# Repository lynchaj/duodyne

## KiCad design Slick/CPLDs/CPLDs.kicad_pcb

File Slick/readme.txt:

The processor.Z80 board is the central processor for the duodyne system.  It uses a Z80 8-bit CPU and includes dual-DMA channels.  It supports Interrupt Mode 2 (IM2) and an extended memory mapper.

Known Issues
1. Missing pull-up resistors on ~DREQ0 and ~DREQ1

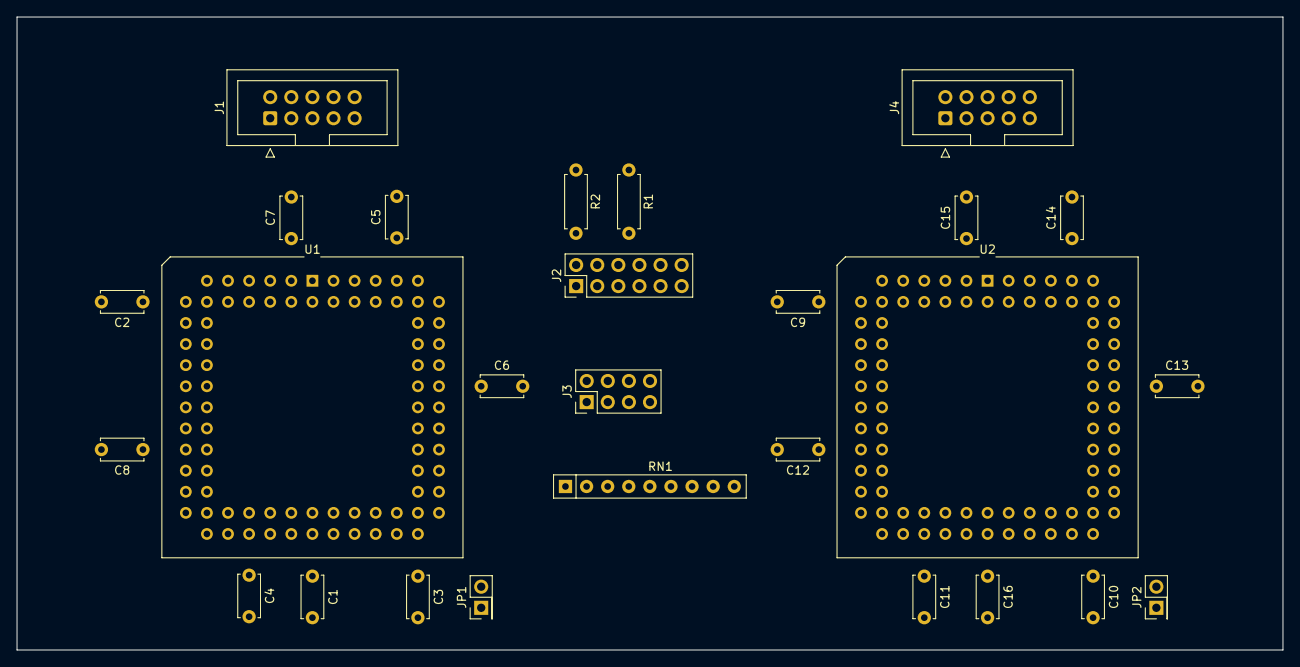
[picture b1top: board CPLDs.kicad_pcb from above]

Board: 2 copper layers, 152.4 x 76.2 mm, 27 parts (0 on the bottom side), 33 nets, no tracks yet.

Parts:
C1, C2, C3, C4, C5, C6, C7, C8, C9, C10, C11, C12, C13, C14, C15, C16: 0.1u; C_Disc_D5.0mm_W2.5mm_P5.00mm
J1: JTAG-1; IDC-Header_2x05_P2.54mm_Vertical
J2: Conn_02x06_Odd_Even; PinHeader_2x06_P2.54mm_Vertical
J3: Conn_02x04_Odd_Even; PinHeader_2x04_P2.54mm_Vertical
J4: JTAG-2; IDC-Header_2x05_P2.54mm_Vertical
JP1, JP2: Jumper_2_Bridged; PinHeader_2x01_P2.54mm_Vertical
R1, R2: 10K; R_Axial_DIN0207_L6.3mm_D2.5mm_P7.62mm_Horizontal
RN1: 10K; R_Array_SIP9
U1, U2: EPM7064S-PLCC-84; PLCC-84_THT-Socket

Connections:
/VCC: JP1.1 (A), JP2.1 (A)
/VCC1: C1.1, C2.1, C3.1, C4.1, C5.1, C6.1, C7.1, C8.1, J1.4, JP1.2 (B), U1.3 (VCCINT), U1.13 (VCCIO), U1.26 (VCCIO), U1.38 (VCCIO), U1.43 (VCCINT), U1.53 (VCCIO), U1.66 (VCCIO), U1.78 (VCCIO)
/VCC2: C9.1, C10.1, C11.1, C12.1, C13.1, C14.1, C15.1, C16.1, J4.4, JP2.2 (B), R1.1, R2.1, RN1.1 (common), U2.3 (VCCINT), U2.13 (VCCIO), U2.26 (VCCIO), U2.38 (VCCIO), U2.43 (VCCINT), U2.53 (VCCIO), U2.66 (VCCIO), U2.78 (VCCIO)
CPU-A1: U1.48 (I/O_4C), U2.34 (I/O_7B)
CPU-A2: U1.25 (I/O_14B), U2.20 (I/O_3A)
CPU-D0: U1.75 (I/O_11D), U2.37 (I/O_4B), U2.46 (I/O_3C)
GND: C1.2, C2.2, C3.2, C4.2, C5.2, C6.2, C7.2, C8.2, C9.2, C10.2, C11.2, C12.2, C13.2, C14.2, C15.2, C16.2, J1.2, J1.10, J4.2, J4.10, U1.2 (OE2/GCLK2), U1.7 (GND), U1.19 (GND), U1.32 (GND), U1.42 (GND), U1.47 (GND), U1.59 (GND), U1.72 (GND), U1.82 (GND), U2.2 (OE2/GCLK2), U2.7 (GND), U2.19 (GND), U2.32 (GND), U2.42 (GND), U2.47 (GND), U2.59 (GND), U2.72 (GND), U2.82 (GND), U2.83 (GCLK1)
IO-SEL: U1.50 (I/O_6C), U2.5 (I/O_15A)
Q2: J2.12, RN1.9 (R8), U2.15 (I/O_7A)
Q3: J2.10, RN1.8 (R7), U2.16 (I/O_6A)
Q4: J2.8, RN1.7 (R6), U2.69 (I/O_6D)
Q5: J2.6, RN1.6 (R5), U2.18 (I/O_4A)
Q6: J2.4, R1.2, U2.81 (I/O_16D)
Q7: J2.2, R2.2, U2.80 (I/O_15D)
R4: J3.8, RN1.5 (R4), U2.25 (I/O_14B)
R5: J3.6, RN1.4 (R3), U2.56 (I/O_12C)
R6: J3.4, RN1.3 (R2), U2.58 (I/O_14C)
R7: J3.2, RN1.2 (R1), U2.11 (I/O_10A)
TCK-1: J1.1, U1.62 (TCK-I/O_16C)
TCK-2: J4.1, U2.62 (TCK-I/O_16C)
TDI-1: J1.9, U1.14 (TDI-I/O_8A)
TDI-2: J4.9, U2.14 (TDI-I/O_8A)
TDO-1: J1.3, U1.71 (TDO-I/O_8D)
TDO-2: J4.3, U2.71 (TDO-I/O_8D)
TMS-1: J1.5, U1.23 (TMS-I/O_16B)
TMS-2: J4.5, U2.23 (TMS-I/O_16B)
ZERO: J2.1, J2.3, J2.5, J2.7, J2.9, J2.11, J3.1, J3.3, J3.5, J3.7
~CPU-IORQ: U1.58 (I/O_14C), U2.61 (I/O_16C)
~CPU-M1: U1.80 (I/O_15D), U2.60 (I/O_15C)
~CPU-RESET: U1.1 (GCLRn), U2.1 (GCLRn)
~CPU-WR: U1.79 (I/O_14D), U2.68 (I/O_5D)
~CS-MAP: U1.27 (I/O_13B), U2.36 (I/O_5B)
~FP-LATCH: U1.24 (I/O_15B), U2.9 (I/O_12A)

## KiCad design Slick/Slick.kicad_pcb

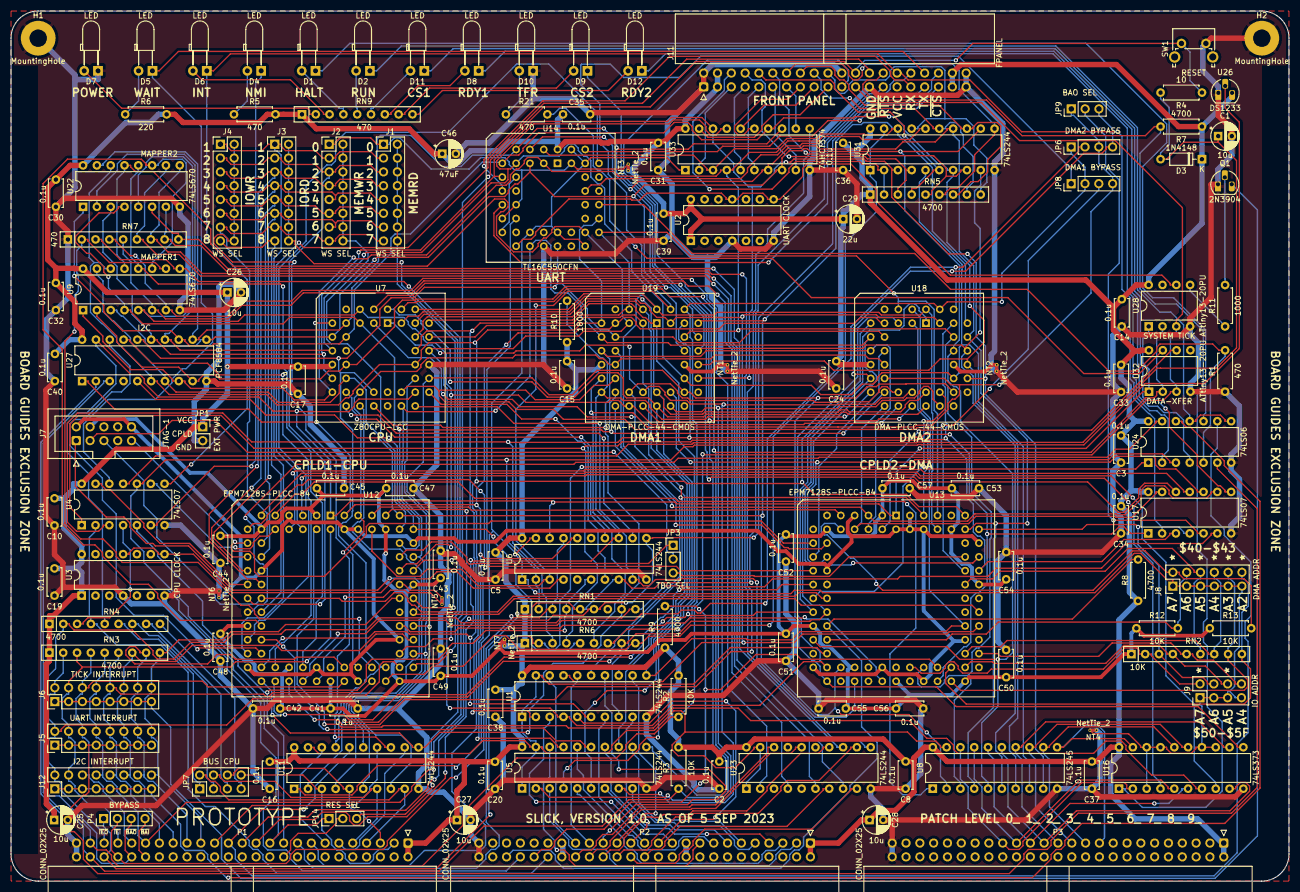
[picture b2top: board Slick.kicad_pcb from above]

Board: 2 copper layers, 235.0 x 160.0 mm, 139 parts (0 on the bottom side), 244 nets.

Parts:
C1, C25, C26, C27, C28: 10u; CP_Radial_D5.0mm_P2.50mm
C2, C3, C5, C8, C10, C14, C15, C16, C17, C19, C20, C24, C30, C31, C32, C33, C34, C35, C36, C37, C38, C39, C40, C41, C42, C43, C44, C45, C47, C48, C49, C50, C51, C52, C53, C54, C55, C56, C57: 0.1u; C_Disc_D5.0mm_W2.5mm_P5.00mm
C29: 22u; CP_Radial_D5.0mm_P2.50mm
C46: 47uF; CP_Radial_D5.0mm_P2.50mm
D1, D2, D4, D5, D6, D7, D8, D9, D10, D11, D12: LED; LED_D3.0mm_Horizontal_O3.81mm_Z2.0mm
D3: 1N4148; D_DO-35_SOD27_P7.62mm_Horizontal
H1, H2: MountingHole; MountingHole_3.2mm_M3_Pad
J1, J2, J3, J4: WS SEL; PinHeader_2x08_P2.54mm_Vertical
J5: UART INTERRUPT; PinHeader_2x08_P2.54mm_Vertical
J6: TICK INTERRUPT; PinHeader_2x08_P2.54mm_Vertical
J7: JTAG-1; IDC-Header_2x05_P2.54mm_Vertical
J8: DMA ADDR; PinHeader_2x06_P2.54mm_Vertical
J9: IO ADDR; PinHeader_2x04_P2.54mm_Vertical
J11: FPANEL; IDC-Header_2x20_P2.54mm_Horizontal
J12: I2C INTERRUPT; PinHeader_2x08_P2.54mm_Vertical
JP1: EXT PWR; PinHeader_2x01_P2.54mm_Vertical
JP3: TDO SEL; PinHeader_1x03_P2.54mm_Vertical
JP6: DMA2 BYPASS; PinHeader_1x04_P2.54mm_Vertical
JP7: BUS CPU; PinHeader_2x04_P2.54mm_Vertical
JP8: DMA1 BYPASS; PinHeader_1x04_P2.54mm_Vertical
JP9: BAO SEL; PinHeader_1x03_P2.54mm_Vertical
JP14: RES SEL; PinHeader_1x03_P2.54mm_Vertical
NT1, NT2, NT3, NT4, NT5, NT6, NT7: NetTie_2; NetTie-2_THT_Pad0.3mm
P1, P2, P3: CONN_02X25; IDC-Header_2x25_P2.54mm_Horizontal
P4: BYPASS; PinHeader_1x04_P2.54mm_Vertical
Q1: 2N3904; TO-92_HandSolder
R1, R5, R21: 470; R_Axial_DIN0207_L6.3mm_D2.5mm_P7.62mm_Horizontal
R2, R3, R12, R13: 10K; R_Axial_DIN0207_L6.3mm_D2.5mm_P7.62mm_Horizontal
R4: 10; R_Axial_DIN0207_L6.3mm_D2.5mm_P7.62mm_Horizontal
R6: 220; R_Axial_DIN0207_L6.3mm_D2.5mm_P7.62mm_Horizontal
R7, R8, R9: 4700; R_Axial_DIN0207_L6.3mm_D2.5mm_P7.62mm_Horizontal
R10: 1800; R_Axial_DIN0207_L6.3mm_D2.5mm_P7.62mm_Horizontal
R11: 1000; R_Axial_DIN0207_L6.3mm_D2.5mm_P7.62mm_Horizontal
RN1, RN3, RN4, RN5, RN6: 4700; R_Array_SIP9
RN2: 10K; R_Array_SIP9
RN7, RN9: 470; R_Array_SIP9
SW1: RESET; SW_Tactile_SPST_Angled_PTS645Vx58-2LFS
U1, U5, U6, U11, U23, U31: 74LS244; DIP-20_W7.62mm
U2: UART CLOCK; DIP-14_W7.62mm
U3: CPU CLOCK; DIP-14_W7.62mm
U4, U17: 74LS07; DIP-14_W7.62mm
U7: Z80CPU-LCC; PLCC-44_THT-Socket
U8: 74LS245; DIP-20_W7.62mm
U9, U22: 74LS670; DIP-16_W7.62mm
U12, U13: EPM7128S-PLCC-84; PLCC-84_THT-Socket
U14: TL16C550CFN; PLCC-44_THT-Socket
U16: 74LS373; DIP-20_W7.62mm
U18, U19: DMA-PLCC-44-CMOS; PLCC-44_THT-Socket
U24: 74LS06; DIP-14_W7.62mm
U26: DS1233; TO-92L_HandSolder
U27: PCF8584; DIP-20_W7.62mm
U28, U32: ATtiny13-20PU; DIP-8_W7.62mm
U33: 74HCT374; DIP-20_W7.62mm

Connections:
1WS: J1.3, J2.3, J3.1, J4.1, U12.30 (I/O_5C)
2WS: J1.5, J2.5, J3.3, J4.3, U12.22 (I/O_1B)
3WS: J1.7, J2.7, J3.5, J4.5, U12.21 (I/O_3B)
4WS: J1.9, J2.9, J3.7, J4.7, U12.18 (I/O_8B)
5WS: J1.11, J2.11, J3.9, J4.9, U12.17 (I/O_9B)
6WS: J1.13, J2.13, J3.11, J4.11, U12.16 (I/O_11B)
7WS: J1.15, J2.15, J3.13, J4.13, U12.15 (I/O_13B)
8WS: J3.15, J4.15, U12.25 (I/O_13C)
10KA: C1.1, D3.2 (A), R4.2, U4.11
470A: D7.2 (A), RN9.2 (R1)
470B: D6.2 (A), RN9.3 (R2)
470C: D1.2 (A), RN9.4 (R3)
470D: D2.2 (A), RN9.5 (R4)
470E: D11.2 (A), RN9.6 (R5)
470F: D8.2 (A), RN9.7 (R6)
470G: D9.2 (A), RN9.8 (R7)
470H: D12.2 (A), RN9.9 (R8)
+12V: P2.19, P2.20
-12V: P2.37, P2.38
/CPLDs/VCC-CPLD: C41.1, C42.1, C43.1, C44.1, C45.1, C47.1, C48.1, C49.1, C50.1, C51.1, C52.1, C53.1, C54.1, C55.1, C56.1, C57.1, J7.4, NT7.2, R12.1, R13.1, RN2.1 (common), U12.3 (VCCINT), U12.13 (VCCIO), U12.26 (VCCIO), U12.38 (VCCIO), U12.43 (VCCINT), U12.53 (VCCIO), U12.66 (VCCIO), U12.78 (VCCIO), U13.3 (VCCINT), U13.13 (VCCIO), U13.26 (VCCIO), U13.38 (VCCIO), U13.43 (VCCINT), U13.53 (VCCIO), U13.66 (VCCIO), U13.78 (VCCIO)
/DMA/GND-DMA1: NT1.2, U19.34 (GND)
/DMA/GND-DMA2: NT2.2, U18.34 (GND)
/fpanel/FP-D0: J11.6, RN5.2 (R1), U31.2 (I0a)
/fpanel/FP-D1: J11.8, RN5.3 (R2), U31.4 (I1a)
/fpanel/FP-D2: J11.10, RN5.4 (R3), U31.6 (I2a)
/fpanel/FP-D3: J11.12, RN5.5 (R4), U31.8 (I3a)
/fpanel/FP-D4: J11.14, RN5.6 (R5), U31.11 (I0b)
/fpanel/FP-D5: J11.16, RN5.7 (R6), U31.13 (I1b)
/fpanel/FP-D6: J11.18, RN5.8 (R7), U31.15 (I2b)
/fpanel/FP-D7: J11.20, RN5.9 (R8), U31.17 (I3b)
A0: P2.35, U1.18 (O0a)
A1: P2.33, U1.16 (O1a)
A2: P2.31, U1.14 (O2a)
A3: P2.29, U1.12 (O3a)
A4: P2.27, U1.9 (O0b)
A5: P2.25, U1.7 (O1b)
A6: P2.23, U1.5 (O2b)
A7: P2.21, U1.3 (O3b)
A8: P2.17, U5.18 (O0a)
A9: P2.15, U5.16 (O1a)
A10: P2.13, U5.14 (O2a)
A11: P2.11, U5.12 (O3a)
A12: P2.9, U5.9 (O0b)
A13: P2.7, U5.7 (O1b)
A14: P2.5, U5.5 (O2b)
A15: P2.3, U5.3 (O3b)
A16: P2.36, U23.18 (O0a)
A17: P2.34, U23.16 (O1a)
A18: P2.32, U23.14 (O2a)
A19: P2.30, U23.12 (O3a)
A20: P2.28, U23.9 (O0b)
A21: P2.26, U23.7 (O1b)
CLK: P1.15, U6.16 (O1a), U7.7 (CLK), U12.83 (GCLK1), U18.8 (CLK), U19.8 (CLK), U27.1 (CLK)
CPU-A0: U1.2 (I0a), U7.34 (A0), U9.14 (Wa), U13.75 (I/O_6H), U14.31 (A0), U18.7 (A0), U19.7 (A0), U22.14 (Wa), U27.6 (A0)
CPU-A1: U1.4 (I1a), U7.35 (A1), U9.13 (Wb), U12.64 (I/O_3G), U13.34 (I/O_13D), U14.30 (A1), U18.5 (A1), U19.5 (A1), U22.13 (Wb)
CPU-A2: U1.6 (I2a), U7.36 (A2), U12.34 (I/O_13D), U13.79 (I/O_13H), U14.29 (A2), U18.4 (A2), U19.4 (A2)
CPU-A3: U1.8 (I3a), U7.37 (A3), U13.81 (I/O_16H), U18.3 (A3), U19.3 (A3)
CPU-A4: U1.11 (I0b), U7.38 (A4), U13.61 (I/O_14F), U18.2 (A4), U19.2 (A4)
CPU-A5: U1.13 (I1b), U7.39 (A5), U13.24 (I/O_14C), U18.1 (A5), U19.1 (A5)
CPU-A6: U1.15 (I2b), U7.40 (A6), U13.80 (I/O_14H), U18.44 (A6), U19.44 (A6)
CPU-A7: U1.17 (I3b), U7.41 (A7), U13.60 (I/O_13F), U18.43 (A7), U19.43 (A7)
CPU-A8: U5.2 (I0a), U7.42 (A8), U18.26 (A8), U19.26 (A8)
CPU-A9: U5.4 (I1a), U7.43 (A9), U18.25 (A9), U19.25 (A9)
CPU-A10: U5.6 (I2a), U7.44 (A10), U18.24 (A10), U19.24 (A10)
CPU-A11: U5.8 (I3a), U7.1 (A11), U18.23 (A11), U19.23 (A11)
CPU-A12: U5.11 (I0b), U7.2 (A12), U18.22 (A12), U19.22 (A12)
CPU-A13: U5.13 (I1b), U7.3 (A13), U18.21 (A13), U19.21 (A13)
CPU-A14: U7.4 (A14), U9.5 (Ra), U12.69 (I/O_11G), U18.20 (A14), U19.20 (A14), U22.5 (Ra)
CPU-A15: U7.5 (A15), U9.4 (Rb), U12.73 (I/O_3H), U18.19 (A15), U19.19 (A15), U22.4 (Rb)
CPU-D0: U7.16 (D0), U8.2 (A0), U9.15 (D1), U12.75 (I/O_6H), U13.36 (I/O_9D), U14.2 (D0), U18.39 (D0), U19.39 (D0), U27.7 (D0), U31.18 (O0a), U33.3 (D0)
CPU-D1: U7.17 (D1), U8.3 (A1), U9.1 (D2), U13.48 (I/O_8E), U14.3 (D1), U18.38 (D1), U19.38 (D1), U27.8 (D1), U31.16 (O1a), U33.4 (D1)
CPU-D2: U7.14 (D2), U8.4 (A2), U9.2 (D3), U13.76 (I/O_8H), U14.4 (D2), U18.37 (D2), U19.37 (D2), U27.9 (D2), U31.14 (O2a), U33.7 (D2)
CPU-D3: U7.9 (D3), U8.5 (A3), U9.3 (D4), U13.28 (I/O_8C), U14.5 (D3), U18.36 (D3), U19.36 (D3), U27.11 (D3), U31.12 (O3a), U33.8 (D3)
CPU-D4: U7.8 (D4), U8.6 (A4), U14.6 (D4), U18.35 (D4), U19.35 (D4), U22.15 (D1), U27.12 (D4), U31.9 (O0b), U33.13 (D4)
CPU-D5: U7.10 (D5), U8.7 (A5), U14.7 (D5), U18.33 (D5), U19.33 (D5), U22.1 (D2), U27.13 (D5), U31.7 (O1b), U33.14 (D5)
CPU-D6: U7.11 (D6), U8.8 (A6), U14.8 (D6), U18.32 (D6), U19.32 (D6), U22.2 (D3), U27.14 (D6), U31.5 (O2b), U33.17 (D6)
CPU-D7: U7.15 (D7), U8.9 (A7), U14.9 (D7), U18.31 (D7), U19.31 (D7), U22.3 (D4), U27.15 (D7), U31.3 (O3b), U33.18 (D7)
D0: P3.33, U8.18 (B0), U16.2 (O0)
D1: P3.31, U8.17 (B1), U16.5 (O1)
D2: P3.29, U8.16 (B2), U16.6 (O2)
D3: P3.27, U8.15 (B3), U16.9 (O3)
D4: P3.25, U8.14 (B4), U16.12 (O4)
D5: P3.23, U8.13 (B5), U16.15 (O5)
D6: P3.21, U8.12 (B6), U16.16 (O6)
D7: P3.19, U8.11 (B7), U16.19 (O7)
DATA-DIR: U8.1 (A->B), U12.9 (I/O_8A)
DATA-XFER: U13.4 (I/O_16A), U32.6 (PB1)
DMA-RDY1: U13.17 (I/O_9B), U19.27 (RDY), U24.3
DMA-RDY2: U13.22 (I/O_1B), U18.27 (RDY), U24.1
FP-LATCH-WR: U12.37 (I/O_8D), U33.11 (Cp)
GND: C1.2, C2.2, C3.2, C5.2, C8.2, C10.2, C14.2, C15.2, C16.2, C17.2, C19.2, C20.2, C24.2, C25.2, C26.2, C27.2, C28.2, C29.2, C30.2, C31.2, C32.2, C33.2, C34.2, C35.2, C36.2, C37.2, C38.2, C39.2, C40.2, C41.2, C42.2, C43.2, C44.2, C45.2, C46.2, C47.2, C48.2, C49.2, C50.2, C51.2, C52.2, C53.2, C54.2, C55.2, C56.2, C57.2, D7.1 (K), D10.1 (K), H1.1, H2.1, J11.1, J11.2, J11.22, J11.25, J11.39, J11.40, JP1.2 (B), NT1.1, NT2.1, NT4.1, NT6.2, P1.49, P1.50, P2.49, P2.50, P3.49, P3.50, Q1.1 (E), R1.1, RN7.1 (common), SW1.2, U1.10 (GND), U2.4, U2.7, U3.4, U3.7, U4.7 (GND), U5.10 (GND), U6.10 (GND), U7.33 (GND), U8.10 (GND), U9.8 (GND), U11.10 (GND), U14.22 (GND), U16.10 (GND), U17.7 (GND), U22.8 (GND), U23.10 (GND), U24.7 (GND), U26.1, U27.10 (VSS), U28.4 (GND), U31.10 (GND), U32.4 (GND), U33.10 (GND)
GND-CPLD: J7.2, J7.10, NT6.1, U12.7 (GNDIO), U12.19 (GNDIO), U12.32 (GNDIO), U12.42 (GNDINT), U12.47 (GNDIO), U12.59 (GNDIO), U12.72 (GNDIO), U12.82 (GNDINT), U12.84 (OE1), U13.2 (OE2/GCLK2), U13.7 (GNDIO), U13.19 (GNDIO), U13.32 (GNDIO), U13.42 (GNDINT), U13.47 (GNDIO), U13.59 (GNDIO), U13.72 (GNDIO), U13.82 (GNDINT), U13.83 (GCLK1), U13.84 (OE1)
I2C-SCL: J11.23, P1.47, R2.1, U27.3 (SCL), U28.3 (PB4), U32.3 (PB4)
I2C-SDA: J11.21, P1.48, R3.1, U27.2 (SDA), U28.2 (PB3), U32.2 (PB3)
IM2-S0: U12.5 (I/O_14A), U16.4 (D1)
IM2-S1: U12.4 (I/O_16A), U16.7 (D2)
IM2-S2: U12.11 (I/O_5A), U16.8 (D3)
INT: R1.2, U14.33 (INTR), U24.5
INT-I2C: U12.24 (I/O_14C), U24.13
IO-SEL: U12.61 (I/O_14F), U13.41 (I/O_1D)
unnamed: D1.1 (K), U24.10
unnamed: D2.1 (K), U24.8, U24.11
unnamed: D4.1 (K), U4.6
unnamed: D4.2 (A), R5.1
unnamed: D5.2 (A), R6.1
unnamed: D8.1 (K), U24.4
unnamed: D9.1 (K), U17.12
unnamed: D10.2 (A), R21.1
unnamed: D11.1 (K), U17.8
unnamed: D12.1 (K), U24.2
unnamed: J5.1, J5.3, J5.5, J5.7, J5.9, J5.11, J5.13, J5.15, U24.6
unnamed: J6.1, J6.3, J6.5, J6.7, J6.9, J6.11, J6.13, J6.15, Q1.3 (C)
unnamed: J11.5, U33.2 (O0)
unnamed: J11.7, U33.5 (O1)
unnamed: J11.9, U33.6 (O2)
unnamed: J11.11, U33.9 (O3)
unnamed: J11.13, U33.12 (O4)
unnamed: J11.15, U33.15 (O5)
unnamed: J11.17, U33.16 (O6)
unnamed: J11.19, U33.19 (O7)
unnamed: J12.1, J12.3, J12.5, J12.7, J12.9, J12.11, J12.13, J12.15, U24.12
unnamed: JP7.1, RN4.6 (R5)
unnamed: JP7.3, RN4.7 (R6)
unnamed: JP7.5, RN4.8 (R7)
unnamed: JP7.7, RN4.9 (R8)
unnamed: JP9.2, U17.5
unnamed: Q1.2 (B), R11.2
unnamed: R11.1, U28.5 (PB0)
unnamed: R21.2, U32.7 (PB2)
unnamed: U14.10 (RCLK), U14.17 (~BAUDOUT)
ONE: J1.1, J2.1, NT3.2, U14.14 (CS0), U14.15 (CS1), U14.43 (~RI)
Q2: J8.12, RN2.9 (R8), U13.52 (I/O_16E)
Q3: J8.10, RN2.8 (R7), U13.51 (I/O_13E)
Q4: J8.8, RN2.7 (R6), U13.57 (I/O_8F)
Q5: J8.6, RN2.6 (R5), U13.67 (I/O_8G)
Q6: J8.4, R12.2, U13.29 (I/O_6C)
Q7: J8.2, R13.2, U13.10 (I/O_6A)
R4: J9.8, RN2.5 (R4), U13.56 (I/O_6F)
R5: J9.6, RN2.4 (R3), U13.55 (I/O_5F)
R6: J9.4, RN2.3 (R2), U13.74 (I/O_5H)
R7: J9.2, RN2.2 (R1), U13.46 (I/O_5E)
RAW-CLK: U3.8, U3.11, U6.4 (I1a)
READY: U4.13, U12.20 (I/O_5B)
RESET: U12.28 (I/O_8C), U14.39 (MR)
RX: J11.31, U14.11 (SIN)
SEL-A14: U5.15 (I2b), U12.29 (I/O_6C)
SEL-A15: U5.17 (I3b), U12.12 (I/O_3A)
TCK: J7.1, U12.62 (TCK-I/O_16F), U13.62 (TCK-I/O_16F)
TDI: J7.9, U12.14 (TDI-I/O_16B), U13.14 (TDI-I/O_16B)
TDO: J7.3, JP3.2
TDO-1: JP3.1, U12.71 (TDO-I/O_16G)
TDO-2: JP3.3, U13.71 (TDO-I/O_16G)
TMS: J7.5, U12.23 (TMS-I/O_16C), U13.23 (TMS-I/O_16C)
TX: J11.33, U14.13 (SOUT)
UART-CLK: U2.8, U2.11, U14.18 (XIN), U28.6 (PB1)
VCC: C2.1, C3.1, C5.1, C8.1, C10.1, C14.1, C15.1, C16.1, C17.1, C19.1, C20.1, C24.1, C25.1, C26.1, C27.1, C28.1, C29.1, C30.1, C31.1, C32.1, C33.1, C34.1, C35.1, C36.1, C37.1, C38.1, C39.1, C40.1, C46.1, D3.1 (K), J11.3, J11.4, J11.37, J11.38, JP1.1 (A), NT3.1, NT7.1, P1.1, P1.2, P2.1, P2.2, P3.1, P3.2, R2.2, R3.2, R5.2, R6.2, R7.1, R8.1, R9.1, R10.1, RN1.1 (common), RN3.1 (common), RN4.1 (common), RN5.1 (common), RN6.1 (common), RN9.1 (common), U1.20 (VCC), U2.1, U2.14, U3.1, U3.14, U4.14 (VCC), U5.20 (VCC), U6.20 (VCC), U7.13 (+5V), U8.20 (VCC), U9.16 (VCC), U11.20 (VCC), U14.44 (VCC), U16.20 (VCC), U17.14 (VCC), U18.13 (VCC), U19.13 (VCC), U22.16 (VCC), U23.20 (VCC), U24.14 (VCC), U26.3, U27.20 (VDD), U28.8 (VCC), U31.20 (VCC), U32.8 (VCC), U33.20 (VCC)
WS-IORD: J3.2, J3.4, J3.6, J3.8, J3.10, J3.12, J3.14, J3.16, U12.57 (I/O_8F)
WS-IOWR: J4.2, J4.4, J4.6, J4.8, J4.10, J4.12, J4.14, J4.16, U12.48 (I/O_8E)
WS-MEMRD: J1.2, J1.4, J1.6, J1.8, J1.10, J1.12, J1.14, J1.16, U12.68 (I/O_9G)
WS-MEMWR: J2.2, J2.4, J2.6, J2.8, J2.10, J2.12, J2.14, J2.16, U12.76 (I/O_8H)
ZERO: J8.1, J8.3, J8.5, J8.7, J8.9, J8.11, J9.1, J9.3, J9.5, J9.7, NT4.2, U6.1 (OEa), U6.19 (OEb), U11.1 (OEa), U14.21 (WR), U14.25 (RD), U14.28 (~ADS), U14.41 (~DSR), U14.42 (~DCD), U16.3 (D0), U16.13 (D4), U16.14 (D5), U16.17 (D6), U16.18 (D7), U33.1 (OE)
mA14: RN7.2 (R1), U9.10 (Q1), U12.50 (I/O_11E)
mA15: RN7.3 (R2), U9.9 (Q2), U12.54 (I/O_3F)
mA16: RN7.4 (R3), U9.7 (Q3), U23.2 (I0a)
mA17: RN7.5 (R4), U9.6 (Q4), U23.4 (I1a)
mA18: RN7.6 (R5), U22.10 (Q1), U23.6 (I2a)
mA19: RN7.7 (R6), U22.9 (Q2), U23.8 (I3a)
mA20: RN7.8 (R7), U22.7 (Q3), U23.11 (I0b)
mA21: RN7.9 (R8), U22.6 (Q4), U23.13 (I1b)
~A-PRIME: NT5.1, U12.41 (I/O_1D)
~A: NT5.2, U12.67 (I/O_8G)
~BAI: P1.40, P4.4
~BAO: P1.42, P4.3, RN1.9 (R8), RN4.2 (R1), U17.6
~BUS-EN: U1.1 (OEa), U1.19 (OEb), U5.1 (OEa), U5.19 (OEb), U8.19 (CE), U11.19 (OEb), U13.31 (I/O_3C), U23.1 (OEa), U23.19 (OEb)
~BUSACK: P1.13, U11.18 (O0a)
~BUSRQ: P1.23, R10.2, U6.13 (I1b), U18.17 (~BUSREQ), U19.17 (~BUSREQ)
~CPU-BUSACK: JP8.3, U7.27 (BUSACK), U13.69 (I/O_11G), U19.16 (~BAI)
~CPU-BUSRQ: U6.7 (O1b), U7.29 (BUSRQ)
~CPU-HALT: U7.20 (HALT), U11.4 (I1a)
~CPU-INT: U6.12 (O3a), U7.18 (INT)
~CPU-IORQ: RN1.8 (R7), U7.22 (IOREQ), U11.11 (I0b), U12.33 (I/O_16D), U13.6 (I/O_13A), U18.11 (~IORQ), U19.11 (~IORQ)
~CPU-M1: U7.31 (M1), U11.8 (I3a), U12.60 (I/O_13F), U13.33 (I/O_16D), U16.11 (LE), U18.30 (~M1), U19.30 (~M1)
~CPU-MREQ: U7.21 (MREQ), U11.13 (I1b), U12.81 (I/O_16H), U18.14 (~MREQ), U19.14 (~MREQ)
~CPU-NMI: U6.14 (O2a), U7.19 (NMI)
~CPU-RD: U7.23 (RD), U11.17 (I3b), U12.52 (I/O_16E), U14.24 (~RD), U18.10 (~RD), U19.10 (~RD), U27.16 (~RD)
~CPU-RESET: RN4.5 (R4), U6.18 (O0a), U7.30 (RESET), U12.1 (GCLRn), U13.1 (GCLRn), U27.19 (~RST), U28.1 (~RESET/PB5), U32.1 (~RESET/PB5)
~CPU-RFSH: U7.32 (RFSH), U11.6 (I2a), U12.56 (I/O_6F)
~CPU-WAIT: U6.9 (O0b), U7.28 (WAIT), U13.37 (I/O_8D)
~CPU-WR: U7.26 (WR), U11.15 (I2b), U12.70 (I/O_13G), U13.70 (I/O_13G), U14.20 (~WR), U18.9 (~WR), U19.9 (~WR)
~CS-I2C-WR: U12.31 (I/O_3C), U27.18 (~WR)
~CS-I2C: U12.36 (I/O_9D), U27.17 (~CS)
~CS-MAP: U12.35 (I/O_11D), U13.20 (I/O_5B)
~CS-UART: U13.18 (I/O_8B), U14.16 (~CS2)
~CTS: J11.35, U14.40 (~CTS)
~DMA-BAO1: JP6.3, JP8.4, JP9.1, RN6.6 (R5), U18.16 (~BAI), U19.15 (~BA0)
~DMA-BAO2: JP6.4, JP9.3, RN6.8 (R7), U11.2 (I0a), U13.25 (I/O_13C), U18.15 (~BA0)
~DMA-CS1: U13.5 (I/O_14A), U17.9, U19.18 (~CE/WAIT)
~DMA-CS2: U13.8 (I/O_11A), U17.13, U18.18 (~CE/WAIT)
~DMA-IEI1: JP8.1, U6.3 (O3b), U12.80 (I/O_14H), U19.42 (IEI)
~DMA-IEO1: JP6.1, JP8.2, RN6.7 (R6), U18.42 (IEI), U19.40 (IEO)
~DMA-IEO2: JP6.2, RN6.9 (R8), U12.51 (I/O_13E), U18.40 (IEO)
~DMA-INT-PULSE1: RN6.3 (R2), U4.3, U13.49 (I/O_9E), U17.1, U19.41 (~INT/PULSE)
~DMA-INT-PULSE2: RN6.4 (R3), U4.1, U13.68 (I/O_9G), U17.3, U18.41 (~INT/PULSE)
~DMA-RESET1: U13.15 (I/O_13B), U19.12 (~RESET)
~DMA-RESET2: U13.16 (I/O_11B), U18.12 (~RESET)
~DREQ0: P2.46, R8.2, U13.27 (I/O_11C)
~DREQ1: P2.42, R9.2, U13.50 (I/O_11E)
~EIRQ0: J5.2, J6.2, J12.2, P1.45, RN3.2 (R1), U12.55 (I/O_5F)
~EIRQ1: J5.4, J6.4, J12.4, P1.43, RN3.3 (R2), U12.2 (OE2/GCLK2)
~EIRQ2: J5.6, J6.6, J12.6, P1.41, RN3.4 (R3), U12.45 (I/O_3E)
~EIRQ3: J5.8, J6.8, J12.8, P1.39, RN3.5 (R4), U12.77 (I/O_11H)
~EIRQ4: J5.10, J6.10, J12.10, P1.37, RN3.6 (R5), U12.49 (I/O_9E)
~EIRQ5: J5.12, J6.12, J12.12, P1.35, RN3.7 (R6), U12.58 (I/O_11F)
~EIRQ6: J5.14, J6.14, J12.14, P1.33, RN3.8 (R7), U12.46 (I/O_5E)
~EIRQ7: J5.16, J6.16, J12.16, P1.31, RN3.9 (R8), U12.65 (I/O_5G)
~EXT-RES: J11.24, JP14.3, R4.1, SW1.1
~FP-LATCH-RD: U12.39 (I/O_5D), U31.1 (OEa), U31.19 (OEb)
~FP-LATCH: U12.79 (I/O_13H), U13.9 (I/O_8A)
~HALT: P1.27, U11.16 (O1a), U24.9
~IEI: P1.44, P4.2, RN1.3 (R2), U6.17 (I3b)
~IEO: P1.46, P4.1, RN6.2 (R1), U17.10
~IM2-EN-OE: J11.28, R7.2, U16.1 (OE)
~IM2-EN: J11.26, U12.6 (I/O_13A)
~IM2-IEO: U12.8 (I/O_11A), U17.11
~IM2-INT: U4.9, U12.10 (I/O_6A)
~INT0-EN: D6.1 (K), J11.30, U4.8, U17.2, U17.4
~INT0: J11.32, P1.17, RN1.5 (R4), U6.8 (I3a)
~INT-I2C: RN6.5 (R4), U12.74 (I/O_5H), U27.5 (~INT)
~IORQ: JP7.2, P1.7, U11.9 (O0b)
~M1: P1.11, U11.12 (O3a)
~MREQ: JP7.4, P1.9, U11.7 (O1b)
~NMI: P1.19, RN1.4 (R3), U4.5, U6.6 (I2a)
~PAGE-EN: U9.11 (~Er), U12.27 (I/O_11C), U22.11 (~Er)
~PAGE-WR: U9.12 (~Ew), U12.40 (I/O_3D), U22.12 (~Ew)
~RD: JP7.8, P1.3, U11.3 (O3b)
~RES-IN: JP14.2, P1.20
~RES-OUT: JP14.1, P1.21, RN1.2 (R1), U4.10, U6.2 (I0a), U26.2
~RFSH: P1.29, U11.14 (O2a)
~RTS: J11.27, U14.36 (~RTS)
~TEND0: P2.44, RN4.3 (R2), U4.4
~TEND1: P2.40, RN4.4 (R3), U4.2
~WAIT-EN: D5.1 (K), J11.34, U4.12
~WAIT: J11.36, P1.25, RN1.6 (R5), U6.11 (I0b)
~WR: JP7.6, P1.5, U11.5 (O2b)

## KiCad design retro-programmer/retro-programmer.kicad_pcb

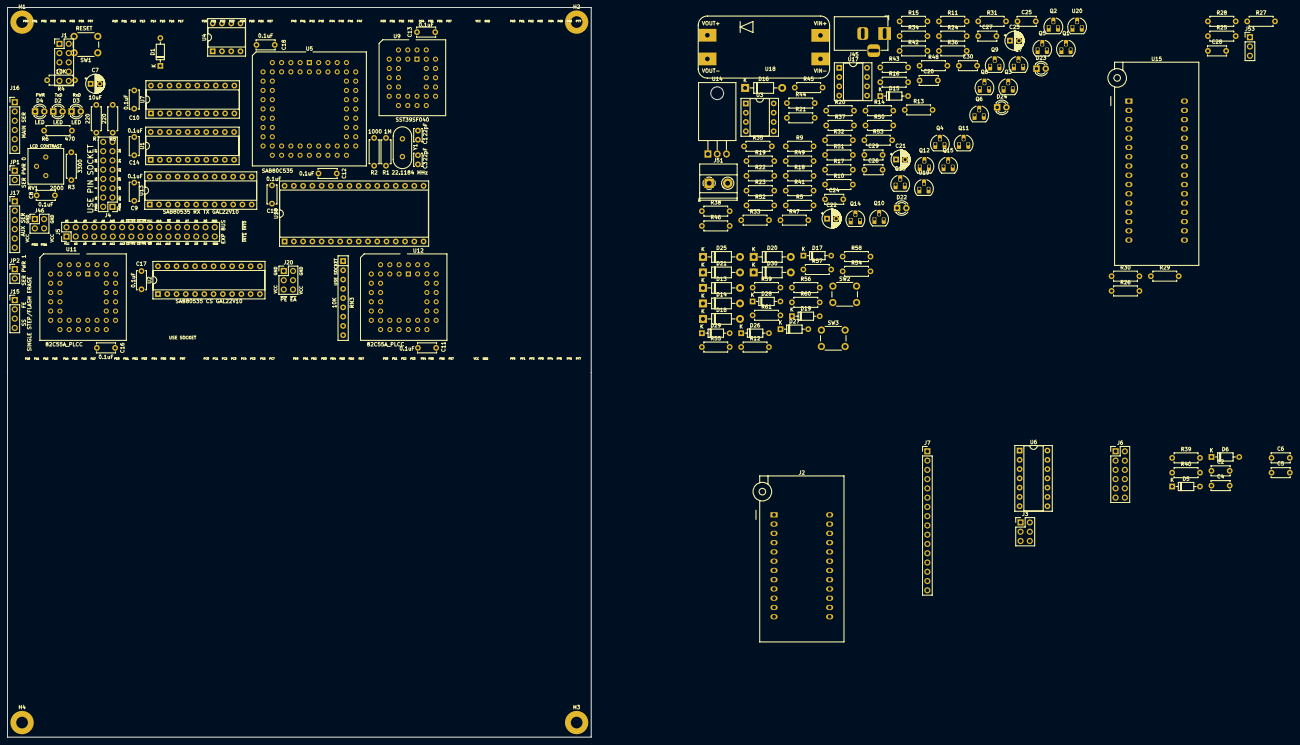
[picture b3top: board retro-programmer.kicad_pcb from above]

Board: 2 copper layers, 160.0 x 200.0 mm, 174 parts (0 on the bottom side), 196 nets, no tracks yet.

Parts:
C1, C3: 22pF; C_Disc_D3.4mm_W2.1mm_P2.50mm
C2, C4, C5, C6, C8, C9, C10, C11, C12, C13, C14, C15, C16, C17, C18, C20, C24, C25, C26, C27, C28, C29, C30: 0.1uF; C_Disc_D5.0mm_W2.5mm_P5.00mm
C7, C21, C22, C23: 10uF; CP_Radial_D5.0mm_P2.50mm
D1, D5, D6, D15, D17, D19, D26, D27, D28, D29: 1N4148; D_DO-35_SOD27_P7.62mm_Horizontal
D2, D3, D4, D22, D23, D24: LED; LED_D3.0mm
D13, D14, D18, D20, D21, D25, D30: 1N4728A; D_DO-41_SOD81_P10.16mm_Horizontal
D16: 1N5819; D_DO-41_SOD81_P10.16mm_Horizontal
H1, H2, H3, H4: MountingHole_Pad; MountingHole_3.2mm_M3_Pad
J1: GPIO BUS; PinHeader_2x05_P2.54mm_Vertical
J2: TTL/CMOS TESTER; DIP_Socket-24_W11.9_W12.7_W15.24_W17.78_W18.5_3M_224-1275-0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
J3: ADC INP; PinHeader_2x03_P2.54mm_Vertical
J4: LCD PORT; PinHeader_2x08_P2.54mm_Vertical
J5: EXP BUS; PinHeader_2x17_P2.54mm_Vertical
J6: PWR PINS; PinHeader_2x06_P2.54mm_Vertical
J7: ALT LCD PORT; PinHeader_1x16_P2.54mm_Vertical
J15: SS FE; PinHeader_1x04_P2.54mm_Vertical
J16: MAIN SER; PinHeader_1x06_P2.54mm_Vertical
J17: AUX SER; PinHeader_1x06_P2.54mm_Vertical
J20: ~{PE} ~{EA}; PinHeader_2x03_P2.54mm_Vertical
J45: Barrel_Jack_MountingPin; BarrelJack_Horizontal
J46: LCD PWR; PinHeader_2x02_P2.54mm_Vertical
J51: 9VDC; TerminalBlock_Phoenix_MKDS-1,5-2-5.08_1x02_P5.08mm_Horizont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
J53: GND32; PinHeader_1x03_P2.54mm_Vertical
JP1: SER PWR 0; PinHeader_1x02_P2.54mm_Vertical
JP2: SER PWR 1; PinHeader_1x02_P2.54mm_Vertical
Q1, Q4, Q5, Q8, Q9, Q12, Q13: 2N3904; TO-92_HandSolder
Q2, Q3, Q6, Q7, Q10, Q11, Q14, Q15: 2N3906; TO-92_HandSolder
R1: 1M; R_Axial_DIN0207_L6.3mm_D2.5mm_P7.62mm_Horizontal
R2, R37: 1000; R_Axial_DIN0207_L6.3mm_D2.5mm_P7.62mm_Horizontal
R3: 3300; R_Axial_DIN0207_L6.3mm_D2.5mm_P7.62mm_Horizontal
R4, R10, R15, R16, R21, R22, R33, R34, R39, R40, R42, R50, R52, R53, R59, R60: 10K; R_Axial_DIN0207_L6.3mm_D2.5mm_P7.62mm_Horizontal
R5, R9, R13, R14, R19, R20, R25, R26, R27, R28, R29, R30, R31, R32, R38: 4700; R_Axial_DIN0207_L6.3mm_D2.5mm_P7.62mm_Horizontal
R6, R41: 470; R_Axial_DIN0207_L6.3mm_D2.5mm_P7.62mm_Horizontal
R7, R8: 220; R_Axial_DIN0207_L6.3mm_D2.5mm_P7.62mm_Horizontal
R11, R17, R18, R23, R24, R35, R36, R48: 22K; R_Axial_DIN0207_L6.3mm_D2.5mm_P7.62mm_Horizontal
R12, R49, R54, R55, R56, R57, R58, R61: 2200; R_Axial_DIN0207_L6.3mm_D2.5mm_P7.62mm_Horizontal
R43: 100K; R_Axial_DIN0207_L6.3mm_D2.5mm_P7.62mm_Horizontal
R44: 39K; R_Axial_DIN0207_L6.3mm_D2.5mm_P7.62mm_Horizontal
R45: 5600; R_Axial_DIN0207_L6.3mm_D2.5mm_P7.62mm_Horizontal
R46, R47: 240; R_Axial_DIN0207_L6.3mm_D2.5mm_P7.62mm_Horizontal
R51: 8200; R_Axial_DIN0207_L6.3mm_D2.5mm_P7.62mm_Horizontal
RN3: 10K; R_Array_SIP9
RV1: 2000; Potentiometer_Bourns_3386P_Vertical
SW1: RESET; SW_PUSH_6mm
SW2: INPUT0; SW_PUSH_6mm
SW3: INPUT1; SW_PUSH_6mm
U1: 74LS273; DIP-20_W7.62mm_Socket
U2, U13: GAL22V10; DIP-24_W7.62mm_Socket
U3, U4: X9C103PZ; DIP-8_W7.62mm_Socket
U5: SAB80C535; PLCC-68_THT-Socket
U6: 74LS14; DIP-14_W7.62mm_Socket
U7: 74LS373; DIP-20_W7.62mm_Socket
U9: SST39SF040; PLCC-32_THT-Socket
U10: AS6C4008-55PCN; DIP-32_W15.24mm_Socket
U11, U12: 82C55A_PLCC; PLCC-44_THT-Socket
U14: LM7805_TO220; TO-220-3_Horizontal_TabDown
U15: 27C080; DIP_Socket-32_W11.9_W12.7_W15.24_W17.78_W18.5_3M_232-1285-0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
U17: LM358; DIP-8_W7.62mm_Socket
U18: MT3608_module
U19, U20: LM317L_TO92; TO-92_HandSolder
Y1: 22.1184 MHz; Crystal_HC49-4H_Vertical

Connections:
/GALS/CS-LCD-WR: U13.10 (I9), U13.22 (O1)
/MCU_SAB80C535/XTAL1: C1.1, R1.1, U5.40 (XTAL1), Y1.1
/MCU_SAB80C535/XTAL2: R2.2, U5.39 (XTAL2)
/Power/9VDC: C20.1, D16.2 (A), J45.1, J51.1
A0: J4.5, J5.5, J7.5, U7.2 (O0), U9.12 (A0), U10.12 (A0), U11.10 (A0), U12.10 (A0)
A1: J4.4, J5.4, J7.4, U7.5 (O1), U9.11 (A1), U10.11 (A1), U11.9 (A1), U12.9 (A1)
A2: J5.3, U7.6 (O2), U9.10 (A2), U10.10 (A2)
A3: J5.6, U7.9 (O3), U9.9 (A3), U10.9 (A3)
A4: J5.9, U7.12 (O4), U9.8 (A4), U10.8 (A4)
A5: J5.2, U7.15 (O5), U9.7 (A5), U10.7 (A5)
A6: J5.7, U7.16 (O6), U9.6 (A6), U10.6 (A6)
A7: J5.8, U7.19 (O7), U9.5 (A7), U10.5 (A7)
A8: J5.10, U2.7 (I6), U5.41 (P2.0), U9.27 (A8), U10.27 (A8)
A9: J5.14, U2.8 (I7), U5.42 (P2.1), U9.26 (A9), U10.26 (A9)
A10: J5.12, U2.9 (I8), U5.43 (P2.2), U9.23 (A10), U10.23 (A10)
A11: J5.21, U2.2 (I1), U5.44 (P2.3), U9.25 (A11), U10.25 (A11)
A12: J5.11, U2.3 (I2), U5.45 (P2.4), U9.4 (A12), U10.4 (A12)
A13: J5.13, U2.4 (I3), U5.46 (P2.5), U9.28 (A13), U10.28 (A13)
A14: J5.22, U2.5 (I4), U5.47 (P2.6), U9.29 (A14), U10.3 (A14)
A15: J5.23, U2.6 (I5), U5.48 (P2.7), U9.22 (CE)
ALE: U5.50 (ALE), U7.11 (LE)
B15: U1.2 (Q0), U9.3 (A15)
B16: U1.5 (Q1), U9.2 (A16)
B17: U1.6 (Q2), U9.30 (A17)
B18: U1.9 (Q3), U9.1 (A18)
C15: U1.12 (Q4), U10.31 (A15)
C16: U1.15 (Q5), U10.2 (A16)
C17: U1.16 (Q6), U10.30 (A17)
C18: U1.19 (Q7), U10.1 (A18)
D0: J4.7, J5.32, J7.7, RN3.2 (R1), U1.3 (D0), U5.52 (P0.0), U7.3 (D0), U9.13 (D0), U10.13 (DQ0), U11.38 (D0), U12.38 (D0)
D1: J4.8, J5.30, J7.8, RN3.3 (R2), U1.4 (D1), U5.53 (P0.1), U7.4 (D1), U9.14 (D1), U10.14 (DQ1), U11.37 (D1), U12.37 (D1)
D2: J4.9, J5.31, J7.9, RN3.4 (R3), U1.7 (D2), U5.54 (P0.2), U7.7 (D2), U9.15 (D2), U10.15 (DQ2), U11.36 (D2), U12.36 (D2)
D3: J4.10, J5.29, J7.10, RN3.5 (R4), U1.8 (D3), U5.55 (P0.3), U7.8 (D3), U9.17 (D3), U10.17 (DQ3), U11.35 (D3), U12.35 (D3)
D4: J4.11, J5.26, J7.11, RN3.6 (R5), U1.13 (D4), U5.56 (P0.4), U7.13 (D4), U9.18 (D4), U10.18 (DQ4), U11.33 (D4), U12.33 (D4)
D5: J4.12, J5.27, J7.12, RN3.7 (R6), U1.14 (D5), U5.57 (P0.5), U7.14 (D5), U9.19 (D5), U10.19 (DQ5), U11.32 (D5), U12.32 (D5)
D6: J4.13, J5.25, J7.13, RN3.8 (R7), U1.17 (D6), U5.58 (P0.6), U7.17 (D6), U9.20 (D6), U10.20 (DQ6), U11.31 (D6), U12.31 (D6)
D7: J4.14, J5.28, J7.14, RN3.9 (R8), U1.18 (D7), U5.59 (P0.7), U7.18 (D7), U9.21 (D7), U10.21 (DQ7), U11.30 (D7), U12.30 (D7)
E: J4.6, J7.6, U13.16 (O7)
GND: C1.2, C2.2, C3.2, C4.2, C5.2, C6.2, C8.2, C9.2, C10.2, C11.2, C12.2, C13.2, C14.2, C15.2, C16.2, C17.2, C18.2, C20.2, C21.2, C22.2, C23.2, C24.2, C25.2, C26.2, C27.2, C28.2, C29.2, C30.2, D4.1 (K), D13.2 (A), D14.2 (A), D18.2 (A), D20.2 (A), D21.2 (A), D22.1 (K), D23.1 (K), D24.1 (K), D25.2 (A), D30.2 (A), H1.1, H2.1, H3.1, H4.1, J1.2, J1.9, J4.16, J5.33, J5.34, J7.16, J15.2, J15.3, J16.1, J17.1, J20.1, J20.2, J45.2, J45.MP (MountPin), J46.2, J51.2, J53.3, Q1.1 (E), Q4.1 (E), Q5.1 (E), Q8.1 (E), Q9.1 (E), Q12.1 (E), Q13.1 (E), R4.2, R25.2, R26.2, R27.2, R28.2, R29.2, R30.2, R42.2, R43.2, R49.2, R51.2, R53.2, RV1.3, SW2.1, SW3.1, U1.10 (GND), U2.12 (GND), U3.4 (VSS), U3.6 (Vl/Rl), U4.4 (VSS), U4.6 (Vl/Rl), U5.12 (VAGND), U5.38 (GND), U6.7 (GND), U7.1 (OE), U7.10 (GND), U9.16 (GND), U10.16 (VSS), U11.8 (GND), U12.8 (GND), U13.12 (GND), U14.2 (GND), U17.4 (V-), U18.2 (VIN-), U18.3 (VOUT-)
GND32: J53.2, U15.16 (GND)
INPUT0: U5.14 (P6.6), U6.2
INPUT1: U5.13 (P6.7), U6.4
LCD-ADJ: C8.1, J4.3, J7.3, RV1.2
LCD-PWR1: J4.1, J7.1, J46.4
LCD-PWR2: J4.2, J7.2, J46.1
unnamed: C2.1, D5.1 (K), R40.2, U6.1
unnamed: C3.1, R1.2, R2.1, Y1.2
unnamed: C4.1, D6.1 (K), R60.2, U6.3
unnamed: D1.2 (A), U5.7 (P4.5)
unnamed: D2.2 (A), R7.1
unnamed: D3.2 (A), R8.1
unnamed: D4.2 (A), R6.1
unnamed: D5.2 (A), R40.1, R59.2, SW2.2
unnamed: D6.2 (A), R39.2, R60.1, SW3.2
unnamed: D13.1 (K), R12.1, U5.15 (P6.5)
unnamed: D15.2 (A), Q2.3 (C)
unnamed: D22.2 (A), R37.2
unnamed: D23.2 (A), R38.2
unnamed: D24.2 (A), R41.2
unnamed: J3.2, U5.20 (P6.0)
unnamed: J3.4, U5.19 (P6.1)
unnamed: J3.6, U5.18 (P6.2)
unnamed: J6.1, U12.24 (PB3)
unnamed: D20.1 (K), J6.2, R56.1
unnamed: J6.3, U12.26 (PB5)
unnamed: D21.1 (K), J6.4, R57.1
unnamed: J6.5, U12.28 (PB7)
unnamed: D25.1 (K), J6.6, R58.1
unnamed: J6.7, U12.17 (PC1)
unnamed: D18.1 (K), J6.8, R55.1
unnamed: J6.9, U12.19 (PC3)
unnamed: D14.1 (K), J6.10, R54.1
unnamed: J6.11, U12.14 (PC5)
unnamed: D30.1 (K), J6.12, R61.1
unnamed: J16.3, JP1.2 (B)
unnamed: J17.3, JP2.2 (B)
unnamed: Q1.2 (B), R5.2
unnamed: Q1.3 (C), R10.2
unnamed: Q2.2 (B), R9.2
unnamed: Q3.2 (B), R10.1, R11.1
unnamed: Q4.2 (B), R13.2
unnamed: Q4.3 (C), R15.2
unnamed: Q5.2 (B), R14.2
unnamed: Q5.3 (C), R16.2
unnamed: Q6.2 (B), R15.1, R17.1
unnamed: Q7.2 (B), R16.1, R18.1
unnamed: Q8.2 (B), R19.2
unnamed: Q8.3 (C), R21.2
unnamed: Q9.2 (B), R20.2
unnamed: Q9.3 (C), R22.2
unnamed: Q10.2 (B), R21.1, R23.1
unnamed: Q11.2 (B), R22.1, R24.1
unnamed: Q12.2 (B), R31.2
unnamed: Q12.3 (C), R33.2
unnamed: Q13.2 (B), R32.2
unnamed: Q13.3 (C), R34.2
unnamed: Q14.2 (B), R33.1, R35.1
unnamed: Q15.2 (B), R34.1, R36.1
unnamed: R3.2, RV1.1
unnamed: R42.1, R44.1, U17.2 (-)
unnamed: R43.1, R45.1, U17.6 (-)
unnamed: R44.2, R46.2, U17.1, U19.1 (ADJ)
unnamed: R45.2, R47.2, U17.7, U20.1 (ADJ)
unnamed: D29.2 (A), U11.14 (PC5)
unnamed: D19.2 (A), U11.17 (PC1)
unnamed: D17.2 (A), U11.19 (PC3)
unnamed: D26.2 (A), U11.24 (PB3)
unnamed: D27.2 (A), U11.26 (PB5)
unnamed: D28.2 (A), U11.28 (PB7)
unnamed: U3.5 (Vw/Rw), U17.3 (+)
unnamed: U4.5 (Vw/Rw), U17.5 (+)
P4.6: J1.4, U5.8 (P4.6)
P4.7: J1.6, U5.9 (P4.7)
RD-2716: R9.1, U5.63 (P5.4)
RESET: C7.2, R4.1, SW1.1, U11.39 (RESET), U12.39 (RESET), U13.11 (I10)
RX-LED: D3.1 (K), U13.17 (O6)
RxD: U5.21 (P3.0/RxD), U13.18 (O5)
RxD-0: J16.4, U13.9 (I8)
RxD-1: J17.4, U13.8 (I7)
T0: U5.25 (P3.4/T0), U13.7 (I6)
T1: J15.4, U5.26 (P3.5/T1)
TX-LED: D2.1 (K), U13.21 (O2)
TxD: U5.22 (P3.1/TxD), U13.6 (I5)
TxD-0: J16.5, U13.19 (O4)
TxD-1: J17.5, U13.20 (O3)
U/~D: U3.2 (U/~D), U4.2 (U/~D), U5.3 (P4.2)
VCC: C5.1, C6.1, C7.1, C9.1, C10.1, C11.1, C12.1, C13.1, C14.1, C15.1, C16.1, C17.1, C18.1, C22.1, C23.1, C24.1, C25.1, C26.1, C27.1, J1.1, J1.10, J4.15, J5.1, J5.20, J7.15, J20.5, J20.6, J46.3, JP1.1 (A), JP2.1 (A), R3.1, R6.2, R7.2, R8.2, R39.1, R41.1, R59.1, RN3.1 (common), SW1.2, U1.20 (VCC), U2.24 (VCC), U3.3 (Vh/Rh), U3.8 (VCC), U4.3 (Vh/Rh), U4.8 (VCC), U5.11 (VAREF), U5.37 (VCC), U5.68 (VCC), U6.14 (VCC), U7.20 (VCC), U9.32 (VCC), U10.32 (VCC), U11.29 (VCC), U12.29 (VCC), U13.24 (VCC), U14.3 (VO)
VCC-ADC: J3.3, R50.2, R51.1
VCC-DIP24: R13.1, U5.62 (P5.5)
VCC-DIP28: R19.1, U5.61 (P5.6)
VCC-DIP32: R31.1, U5.60 (P5.7)
VCC-OUT: C30.1, Q2.1 (E), Q6.1 (E), Q10.1 (E), Q14.1 (E), R17.2, R23.2, R35.2, R37.1, R47.1, R50.1, U20.2 (VO)
VIN: C21.1, D16.1 (K), R52.1, U14.1 (VI), U18.1 (VIN+), U20.3 (VI)
VIN-ADC: J3.1, R52.2, R53.1
VOUT: U17.8 (V+), U18.4 (VOUT+), U19.3 (VI)
VPP-2716: R5.1, U5.67 (P5.0)
VPP-2732: R14.1, U5.66 (P5.1)
VPP-ADC: J3.5, R48.2, R49.1
VPP-DIP28: R20.1, U5.65 (P5.2)
VPP-DIP32: R32.1, U5.64 (P5.3)
VPP-OUT: C29.1, Q3.1 (E), Q7.1 (E), Q11.1 (E), Q15.1 (E), R11.2, R18.2, R24.2, R36.2, R38.1, R46.1, R48.1, U19.2 (VO)
zA0: J2.1, U11.5 (PA0), U12.5 (PA0), U15.12 (A0)
zA1: J2.2, U11.4 (PA1), U12.4 (PA1), U15.11 (A1)
zA2: J2.3, U11.3 (PA2), U12.3 (PA2), U15.10 (A2)
zA3: J2.4, U11.2 (PA3), U12.2 (PA3), U15.9 (A3)
zA4: J2.5, U11.44 (PA4), U12.44 (PA4), U15.8 (A4)
zA5: J2.6, U11.43 (PA5), U12.43 (PA5), U15.7 (A5)
zA6: J2.7, U11.42 (PA6), U12.42 (PA6), U15.6 (A6)
zA7: J2.8, U11.41 (PA7), U12.41 (PA7), U15.5 (A7)
zA8: J2.9, U11.20 (PB0), U12.20 (PB0), U15.27 (A8)
zA9: J2.10, U11.21 (PB1), U12.21 (PB1), U15.26 (A9)
zA10: J2.11, U11.22 (PB2), U12.22 (PB2), U15.23 (A10)
zA11: D15.1 (K), D26.1 (K), J2.13, Q3.3 (C), R26.1, R56.2, U15.25 (A11)
zA12: J2.14, U11.25 (PB4), U12.25 (PB4), U15.4 (A12)
zA13: D27.1 (K), J2.15, Q6.3 (C), R27.1, R57.2, U15.28 (A13)
zA14: J2.16, U11.27 (PB6), U12.27 (PB6), U15.29 (A14)
zA15: D28.1 (K), J2.17, Q11.3 (C), R28.1, R58.2, U15.3 (A15)
zA16: J2.18, U11.16 (PC0), U12.16 (PC0), U15.2 (A16)
zA17: D19.1 (K), J2.19, Q10.3 (C), R29.1, R55.2, U15.30 (A17)
zA18: J2.20, U11.18 (PC2), U12.18 (PC2), U15.31 (A18)
zA19: D17.1 (K), J2.21, Q15.3 (C), R30.1, R54.2, U15.1 (A19)
zCE: U5.1 (P4.0), U5.16 (P6.4), U15.22 (~CE)
zD0: U5.36 (P1.0/~INT3/CC0), U15.13 (D0)
zD1: U5.35 (P1.1/INT4/CC1), U15.14 (D1)
zD2: U5.34 (P1.2/INT5/CC2), U15.15 (D2)
zD3: U5.33 (P1.3/INT6/CC3), U15.17 (D3)
zD4: U5.32 (P1.4/~INT2), U15.18 (D4)
zD5: U5.31 (P1.5/T2EX), U15.19 (D5)
zD6: U5.30 (P1.6/CLKOUT), U15.20 (D6)
zD7: U5.29 (P1.7/T2), U15.21 (D7)
zGND: J2.12, J53.1, U11.15 (PC4), U12.15 (PC4)
zOE: D1.1 (K), Q7.3 (C), R12.2, R25.1, U15.24 (~OE)
zSPARE0: J1.8, J2.22, U11.13 (PC6), U12.13 (PC6)
zSPARE1: J1.7, J2.23, U11.11 (PC7), U12.11 (PC7)
zVCC: C28.1, D29.1 (K), J2.24, Q14.3 (C), R61.2, U15.32 (VCC)
~CS-DP0: U3.7 (~CS), U5.5 (P4.3)
~CS-DP1: U4.7 (~CS), U5.6 (P4.4)
~CS-LATCH: U1.11 (Cp), U2.15 (O8)
~CS-LCD: U2.16 (O7), U13.5 (I4)
~CS-P0: J5.18, U2.20 (O3)
~CS-P1: J5.17, U2.19 (O4)
~CS-P2: J5.15, U2.18 (O5)
~CS-P3: J5.16, U2.17 (O6)
~CS-PPI0: U2.22 (O1), U11.7 (~CS)
~CS-PPI1: U2.21 (O2), U12.7 (~CS)
~CS-RAM: U2.23 (O0), U10.22 (CE#)
~EA: J20.4, U5.51 (~EA)
~INC: U3.1 (~INC), U4.1 (~INC), U5.2 (P4.1)
~INT0: J1.3, U5.23 (P3.2/~INT0)
~INT1: J1.5, J15.1, U5.24 (P3.3/~INT1)
~OE: J5.24, U9.24 (OE), U10.24 (OE#), U11.6 (~RD), U12.6 (~RD), U13.23 (O0)
~PE: J20.3, U5.4 (~PE)
~PSEN: U5.49 (~PSEN), U13.3 (I2)
~RD: U5.28 (P3.7/~RD), U13.2 (I1)
~RESET: U1.1 (~Mr), U5.10 (~RESET), U13.15 (O8)
~WR: J5.19, U5.27 (P3.6/~WR), U9.31 (PGM), U10.29 (WE#), U11.40 (~WR), U12.40 (~WR), U13.4 (I3)
